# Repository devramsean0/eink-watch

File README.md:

# eink-watch
A dirt simple, phone independent Eink Watch

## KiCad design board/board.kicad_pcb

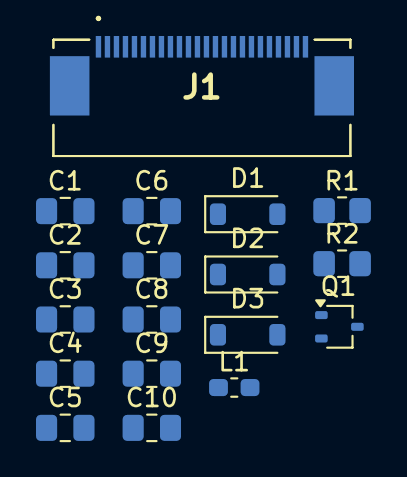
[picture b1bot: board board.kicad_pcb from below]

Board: 2 copper layers, 18 parts (18 on the bottom side), 13 nets, no tracks yet.

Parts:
C1, C2, C3, C4, C5, C6, C7, C9: 1uF 50V; C_0805_2012Metric_Pad1.18x1.45mm_HandSolder
C8, C10: 4.7uF 50V; C_0805_2012Metric_Pad1.18x1.45mm_HandSolder
D1, D2, D3: MBR0530; D_SOD-123
J1: 24pin FPC, 0.5mm; AFC07S24ECA00
L1: 10uH 1A Wire Wound; L_0603_1608Metric_Pad1.05x0.95mm_HandSolder
Q1: Si1308EDL; SOT-323_SC-70
R1: 10k; R_0805_2012Metric_Pad1.20x1.40mm_HandSolder
R2: 3; R_0805_2012Metric_Pad1.20x1.40mm_HandSolder

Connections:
+3V3: C2.2, C10.1, J1.15, J1.16, L1.1
/GDR: J1.2, Q1.1 (G), R1.1
/PREVGH: C9.1, D3.1 (K), J1.21
/PREVGL: C6.2, D1.2 (A), J1.23
/VCOM: C7.2, J1.24
GND: C1.1, C2.1, C3.1, C4.1, C5.1, C6.1, C7.1, C9.2, C10.2, D2.1 (K), J1.8, J1.17, R1.2, R2.2
unnamed: C8.1, D1.1 (K), D2.2 (A)
unnamed: C8.2, D3.2 (A), L1.2, Q1.3 (D)
unnamed: C1.2, J1.5
unnamed: C3.2, J1.18
unnamed: C4.2, J1.20
unnamed: C5.2, J1.22
unnamed: Q1.2 (S), R2.1

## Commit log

2025-05-15 Create LICENSE
2025-05-15 Start writing the Journal
2025-05-15 Fix Image syntax
2025-05-16 Eink Schematic (V1)
2025-05-16 Start assigning footprints
2025-05-16 Continue work
2025-05-18 Hello Power!
2025-05-18 [ImgBot] Optimize images
    *Total -- 166.16kb -> 128.54kb (22.64%)
    /journal/images/eink-schematic-v1.png -- 40.51kb -> 18.04kb (55.48%)
    /journal/images/power-schematic-v1.png -- 26.67kb -> 13.25kb (50.32%)
    /journal/images/waveshare-site.png -- 98.97kb -> 97.25kb (1.74%)
